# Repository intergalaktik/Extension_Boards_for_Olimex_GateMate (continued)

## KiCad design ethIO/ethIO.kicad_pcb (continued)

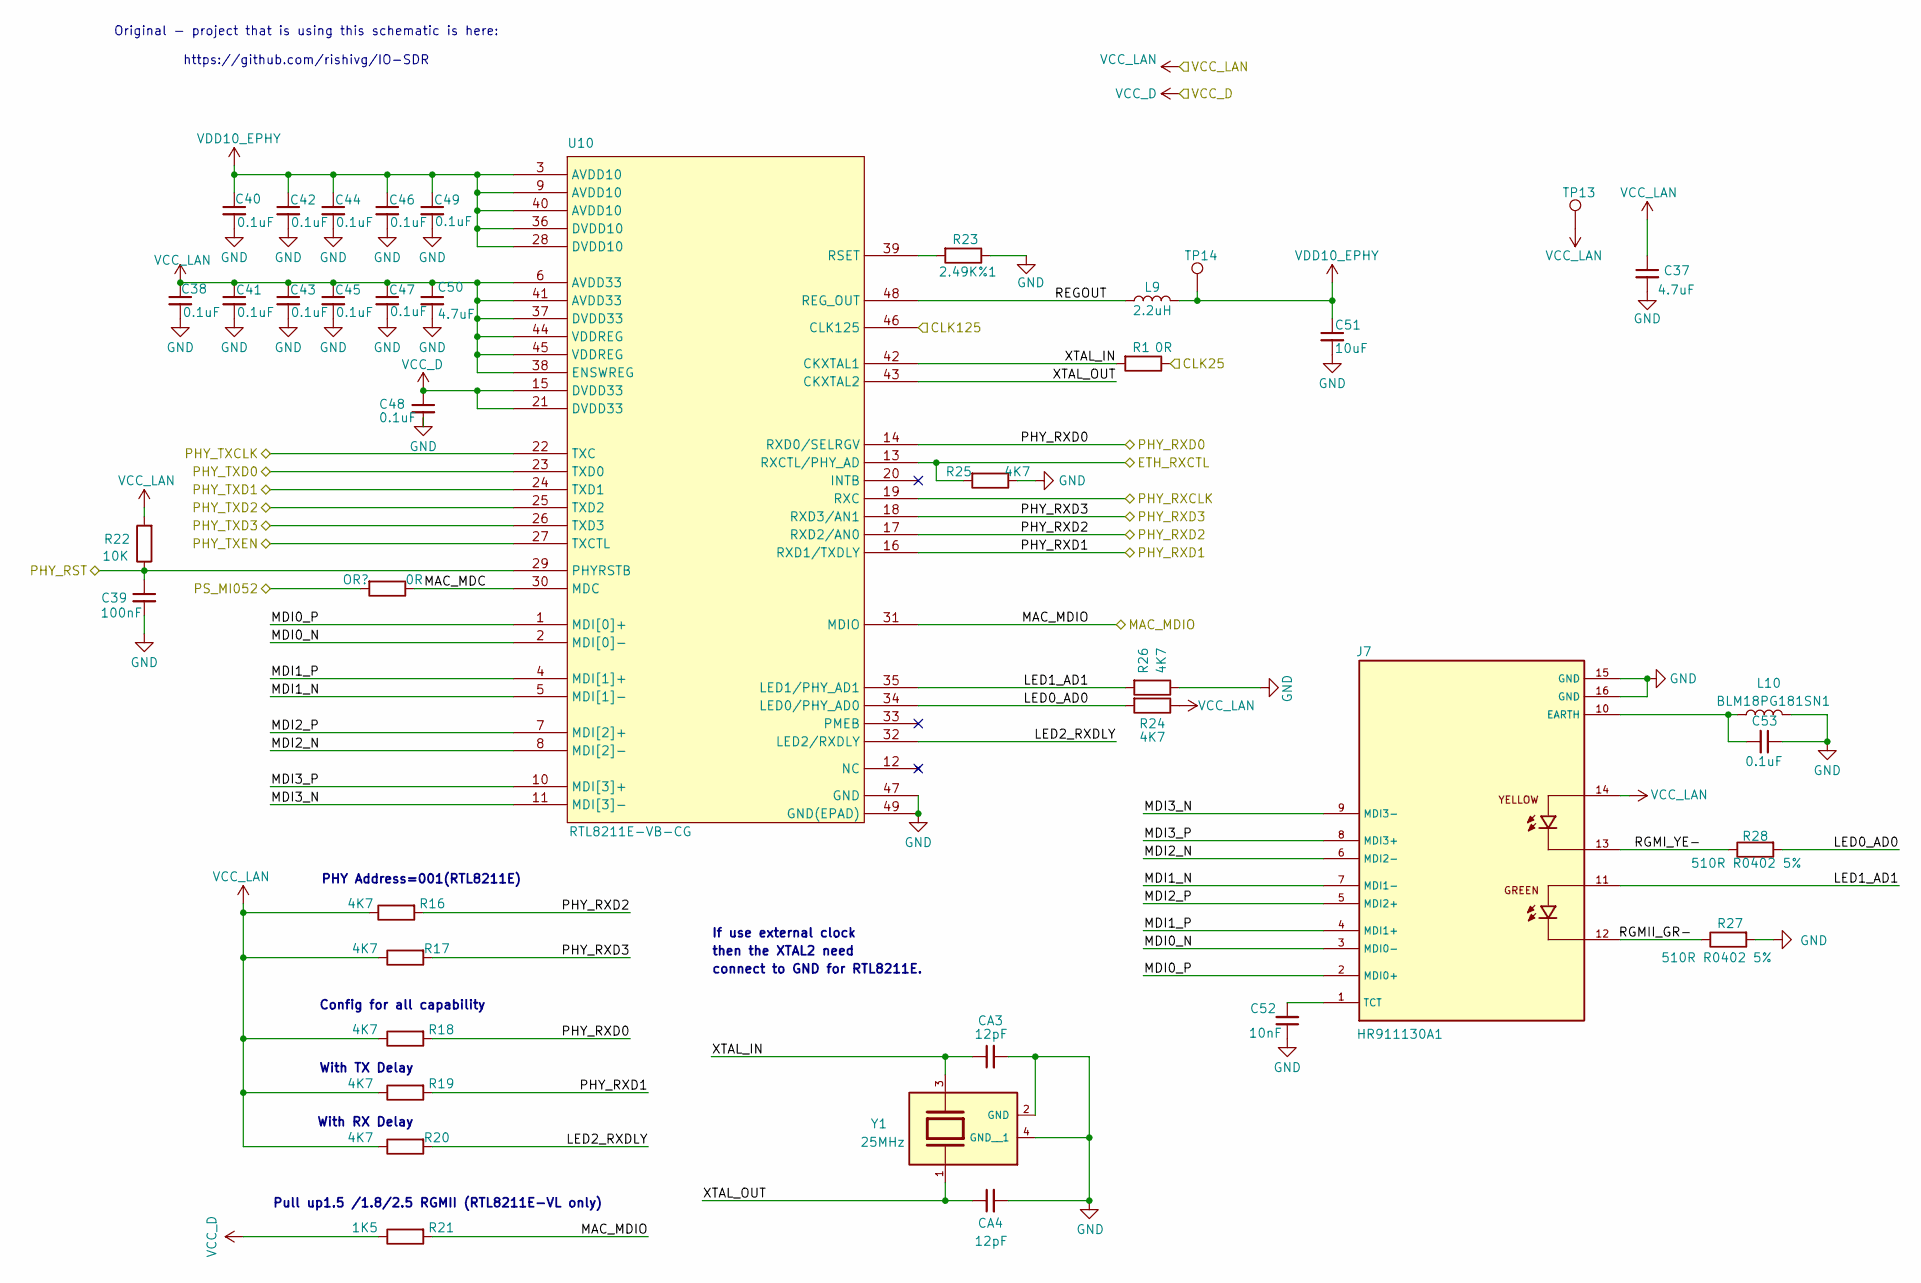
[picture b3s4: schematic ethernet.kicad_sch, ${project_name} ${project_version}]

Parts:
C37, C50: 4.7uF; C_0603_1608Metric_Pad1.08x0.95mm_HandSolder
C38, C40, C41, C42, C43, C44, C45, C46, C47, C48, C49: 0.1uF; C_0402_1005Metric_Pad0.74x0.62mm_HandSolder
C39: 100nF; C_0402_1005Metric_Pad0.74x0.62mm_HandSolder
C51: 10uF; C_0805_2012Metric_Pad1.18x1.45mm_HandSolder
C52: 10nF; C_0402_1005Metric_Pad0.74x0.62mm_HandSolder
C53: 0.1uF; C_0805_2012Metric_Pad1.18x1.45mm_HandSolder
CA3, CA4: 12pF; C_0402_1005Metric_Pad0.74x0.62mm_HandSolder
J7: HR911130A1; HR911130A_HAN
L9: 2.2uH; L_0603_1608Metric_Pad1.05x0.95mm_HandSolder
L10: BLM18PG181SN1; L_0603_1608Metric_Pad1.05x0.95mm_HandSolder
R1: 0R; R_0402_1005Metric_Pad0.72x0.64mm_HandSolder
R16, R17, R18, R19, R20, R24, R25, R26: 4K7; R_0402_1005Metric_Pad0.72x0.64mm_HandSolder
R21: 1K5; R_0402_1005Metric_Pad0.72x0.64mm_HandSolder
R22: 10K; R_0402_1005Metric_Pad0.72x0.64mm_HandSolder
R23: 2.49K%1; R_0402_1005Metric_Pad0.72x0.64mm_HandSolder
R27, R28: 510R R0402 5%; R_0402_1005Metric_Pad0.72x0.64mm_HandSolder
RA5: 0R; R_0603_1608Metric_Pad0.98x0.95mm_HandSolder
TP13, TP14: TestPoint; TestPoint_Pad_D1.0mm
U10: RTL8211E-VB-CG
Y1: 25MHz; Crystal_SMD_SeikoEpson_TSX3225-4Pin_3.2x2.5mm; PARTREV N/A

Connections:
+VCC_HIGH: C37.1, C38.1, C41.1, C43.1, C45.1, C47.1, C50.1, J7.14, R16.1, R17.1, R18.1, R19.1, R20.1, R22.2, R24.1, TP13.1, U10.6 (AVDD33), U10.37 (DVDD33), U10.38 (ENSWREG), U10.41 (AVDD33), U10.44 (VDDREG), U10.45 (VDDREG); also elsewhere on the board
+VCC_LOW: C48.1, R21.1, U10.15 (DVDD33), U10.21 (DVDD33); also elsewhere on the board
/Main Sheet/Ethernet/LED0_AD0: R24.2, R28.2, U10.34 (LED0/PHY_AD0)
/Main Sheet/Ethernet/LED1_AD1: J7.11, R26.2, U10.35 (LED1/PHY_AD1)
/Main Sheet/Ethernet/LED2_RXDLY: R20.2, U10.32 (LED2/RXDLY)
/Main Sheet/Ethernet/MAC_MDC: U10.30 (MDC); also elsewhere on the board
/Main Sheet/Ethernet/MDI0_N: J7.3 (MDI0-), U10.2 (MDI[0]-)
/Main Sheet/Ethernet/MDI0_P: J7.2 (MDI0+), U10.1 (MDI[0]+)
/Main Sheet/Ethernet/MDI1_N: J7.7 (MDI1-), U10.5 (MDI[1]-)
/Main Sheet/Ethernet/MDI1_P: J7.4 (MDI1+), U10.4 (MDI[1]+)
/Main Sheet/Ethernet/MDI2_N: J7.6 (MDI2-), U10.8 (MDI[2]-)
/Main Sheet/Ethernet/MDI2_P: J7.5 (MDI2+), U10.7 (MDI[2]+)
/Main Sheet/Ethernet/MDI3_N: J7.9 (MDI3-), U10.11 (MDI[3]-)
/Main Sheet/Ethernet/MDI3_P: J7.8 (MDI3+), U10.10 (MDI[3]+)
/Main Sheet/Ethernet/REGOUT: L9.1, U10.48 (REG_OUT)
/Main Sheet/Ethernet/RGMII_GR-: J7.12, R27.1
/Main Sheet/Ethernet/RGMI_YE-: J7.13, R28.1
/Main Sheet/Ethernet/XTAL_IN: CA3.1, R1.2, U10.42 (CKXTAL1), Y1.3
/Main Sheet/Ethernet/XTAL_OUT: CA4.1, U10.43 (CKXTAL2), Y1.1
/Main Sheet/NB_A0_0P: R25.2, U10.13 (RXCTL/PHY_AD); also elsewhere on the board
/Main Sheet/NB_A1_1P: R21.2, U10.31 (MDIO); also elsewhere on the board
/Main Sheet/NB_A2_2P: R16.2, U10.17 (RXD2/AN0); also elsewhere on the board
/Main Sheet/NB_A3_3P: U10.19 (RXC); also elsewhere on the board
/Main Sheet/NB_A4_4P: U10.23 (TXD0); also elsewhere on the board
/Main Sheet/NB_A5_5P: U10.25 (TXD2); also elsewhere on the board
/Main Sheet/NB_A6_6P: U10.27 (TXCTL); also elsewhere on the board
/Main Sheet/NB_A8_8P: U10.46 (CLK125); also elsewhere on the board
/Main Sheet/NB_B0_0N: R18.2, U10.14 (RXD0/SELRGV); also elsewhere on the board
/Main Sheet/NB_B1_1N: R19.2, U10.16 (RXD1/TXDLY); also elsewhere on the board
/Main Sheet/NB_B2_2N: R17.2, U10.18 (RXD3/AN1); also elsewhere on the board
/Main Sheet/NB_B3_3N: U10.22 (TXC); also elsewhere on the board
/Main Sheet/NB_B4_4N: U10.24 (TXD1); also elsewhere on the board
/Main Sheet/NB_B5_5N: U10.26 (TXD3); also elsewhere on the board
/Main Sheet/NB_B6_6N: C39.1, R22.1, U10.29 (PHYRSTB); also elsewhere on the board
/Main Sheet/NB_B7_7N: R1.1; also elsewhere on the board
GND: C37.2, C38.2, C39.2, C40.2, C41.2, C42.2, C43.2, C44.2, C45.2, C46.2, C47.2, C48.2, C49.2, C50.2, C51.2, C52.1, C53.1, CA3.2, CA4.2, J7.15 (GND), J7.16 (GND), L10.1, R23.1, R25.1, R26.1, R27.2, U10.47 (GND), U10.49 (GND(EPAD)), Y1.2 (GND), Y1.4 (GND__1); also elsewhere on the board
unnamed: C53.2, J7.10 (EARTH), L10.2
unnamed: C52.2, J7.1 (TCT)
unnamed: R23.2, U10.39 (RSET)
VDD10_EPHY: C40.1, C42.1, C44.1, C46.1, C49.1, C51.1, L9.2, TP14.1, U10.3 (AVDD10), U10.9 (AVDD10), U10.28 (DVDD10), U10.36 (DVDD10), U10.40 (AVDD10)

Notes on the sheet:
then the XTAL2 need
PHY Address=001(RTL8211E)
With RX Delay
Pull up1.5 /1.8/2.5 RGMII (RTL8211E-VL only)
connect to GND for RTL8211E.
If use external clock
Original - project that is using this schematic is here: https://github.com/rishivg/IO-SDR
Config for all capability
With TX Delay

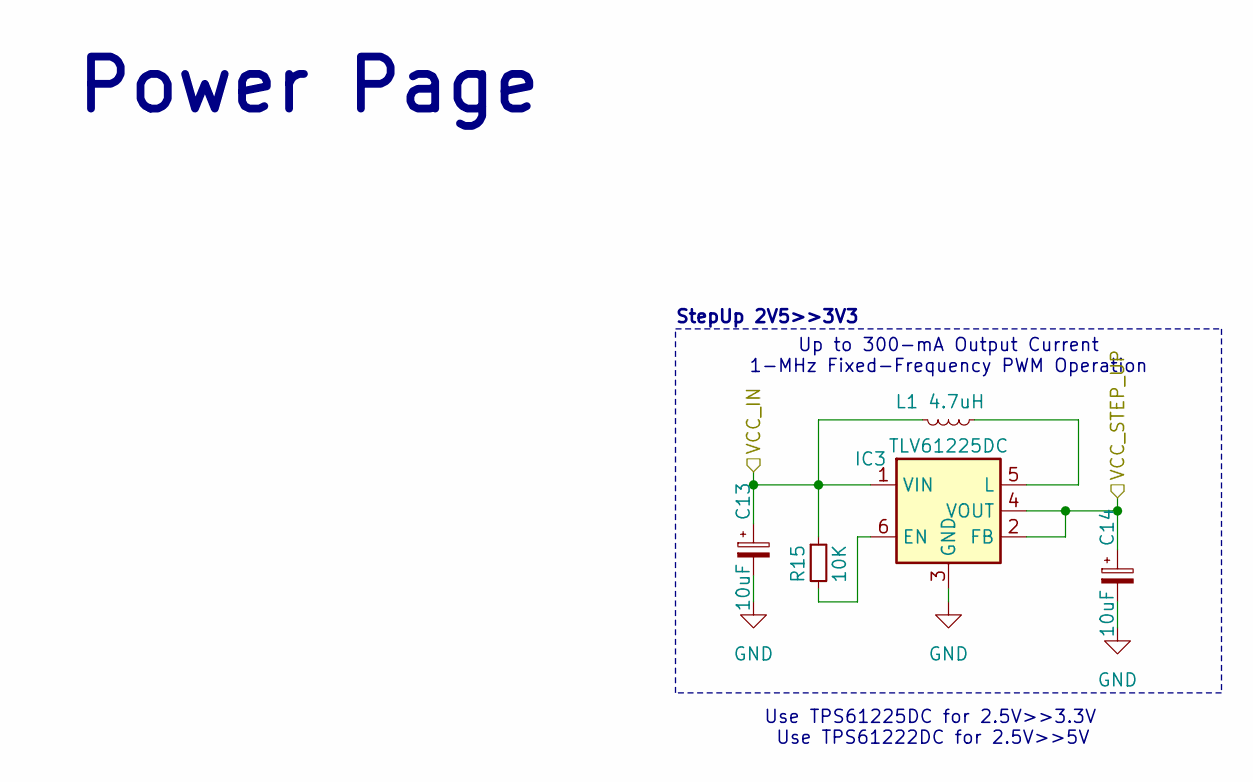
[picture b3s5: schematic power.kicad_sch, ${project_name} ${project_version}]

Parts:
C13, C14: 10uF; C_0603_1608Metric
IC3: TLV61225DC; SOT-363_SC-70-6
L1: 4.7uH; L_0603_1608Metric
R15: 10K; R_0402_1005Metric; MPN RC0603FR-071K1L; Mouser 603-RC0603FR-071K1L

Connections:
+VCC_HIGH: C14.1, IC3.2 (FB), IC3.4 (VOUT); also elsewhere on the board
+VCC_LOW: C13.1, IC3.1 (VIN), L1.2, R15.1; also elsewhere on the board
GND: C13.2, C14.2, IC3.3 (GND); also elsewhere on the board
unnamed: IC3.6 (EN), R15.2
unnamed: IC3.5 (L), L1.1

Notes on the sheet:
Up to 300-mA Output Current 1-MHz Fixed-Frequency PWM Operation
Use TPS61222DC for 2.5V>>5V
Power Page
StepUp 2V5>>3V3
Use TPS61225DC for 2.5V>>3.3V

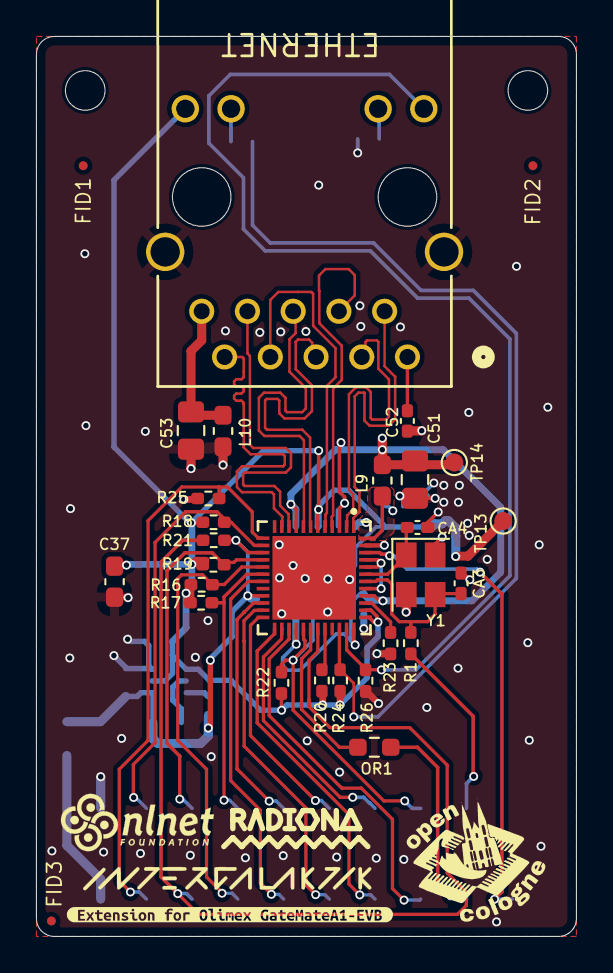
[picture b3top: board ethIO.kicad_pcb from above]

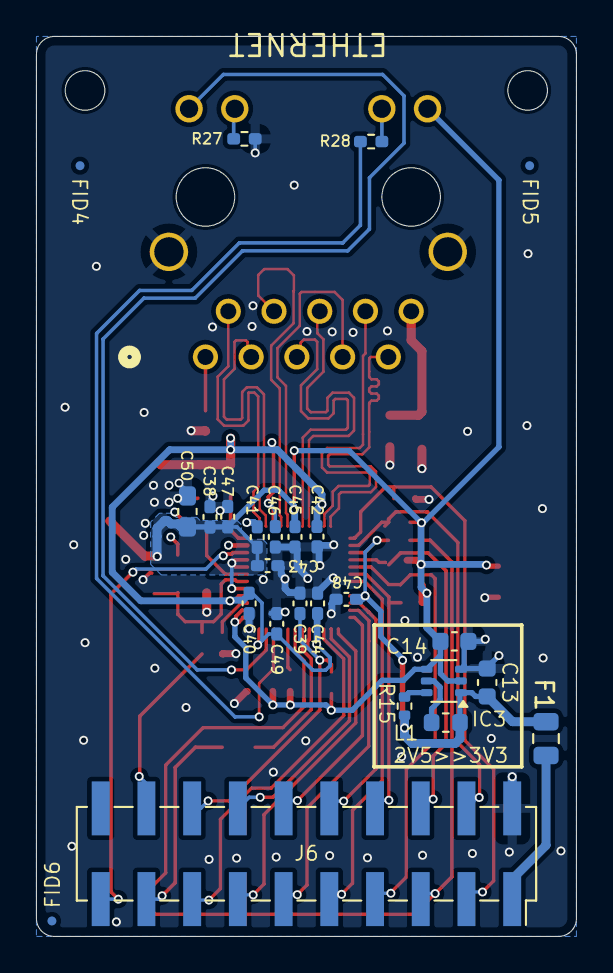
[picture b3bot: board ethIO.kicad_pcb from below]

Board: 4 copper layers, 30.0 x 50.0 mm, 61 parts (25 on the bottom side), 44 nets.

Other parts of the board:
OR1: 0R; R_0603_1608Metric_Pad0.98x0.95mm_HandSolder
kibuzzard-674D68C8: G***; kibuzzard-674D68C8

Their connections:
/Main Sheet/Ethernet/MAC_MDC: OR1.1; also elsewhere on the board
/Main Sheet/NB_A7_7P: OR1.2; also elsewhere on the board

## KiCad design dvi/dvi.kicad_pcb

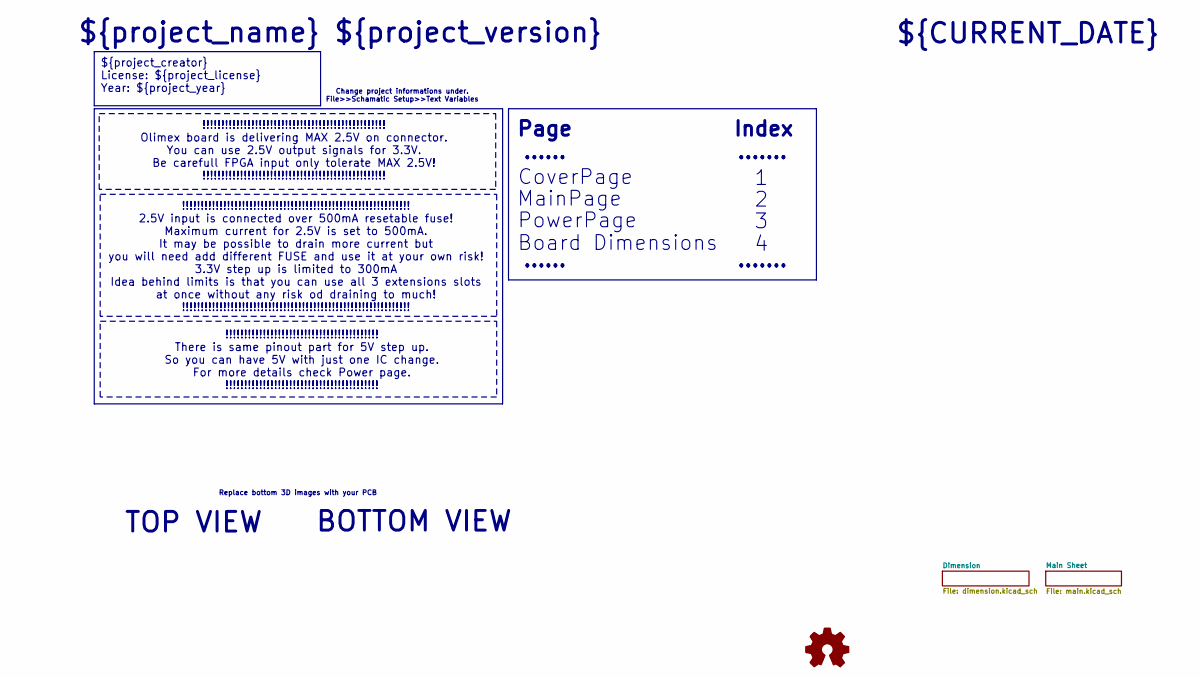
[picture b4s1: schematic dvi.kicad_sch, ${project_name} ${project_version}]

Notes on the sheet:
${project_creator} License: ${project_license} Year: ${project_year}
BOTTOM VIEW
Replace bottom 3D images with your PCB
Index
!!!!!!!!!!!!!!!!!!!!!!!!!!!!!!!!!!!!!!!!!!!!!!!!!!!!!!!!!!!!! 2.5V input is connected over 500mA resetable fuse! Maximum current for 2.5V is set to 500mA. It may be possible to drain more current but you will need add different FUSE and use it at your own risk! 3.3V step up is limited to 300mA Idea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
!!!!!!!!!!!!!!!!!!!!!!!!!!!!!!!!!!!!!!!!!!!!!!!!! Olimex board is delivering MAX 2.5V on connector. You can use 2.5V output signals for 3.3V. Be carefull FPGA input only tolerate MAX 2.5V! !!!!!!!!!!!!!!!!!!!!!!!!!!!!!!!!!!!!!!!!!!!!!!!!!
!!!!!!!!!!!!!!!!!!!!!!!!!!!!!!!!!!!!!!!!! There is same pinout part for 5V step up. So you can have 5V with just one IC change. For more details check Power page. !!!!!!!!!!!!!!!!!!!!!!!!!!!!!!!!!!!!!!!!!
......
PowerPage
Change project informations under. File>>Schamatic Setup>>Text Variables
.......
CoverPage
Board Dimensions
MainPage
${CURRENT_DATE}
${project_name} ${project_version}
TOP VIEW
Page

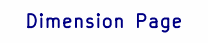
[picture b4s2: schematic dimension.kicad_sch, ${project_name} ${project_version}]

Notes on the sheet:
Dimension Page

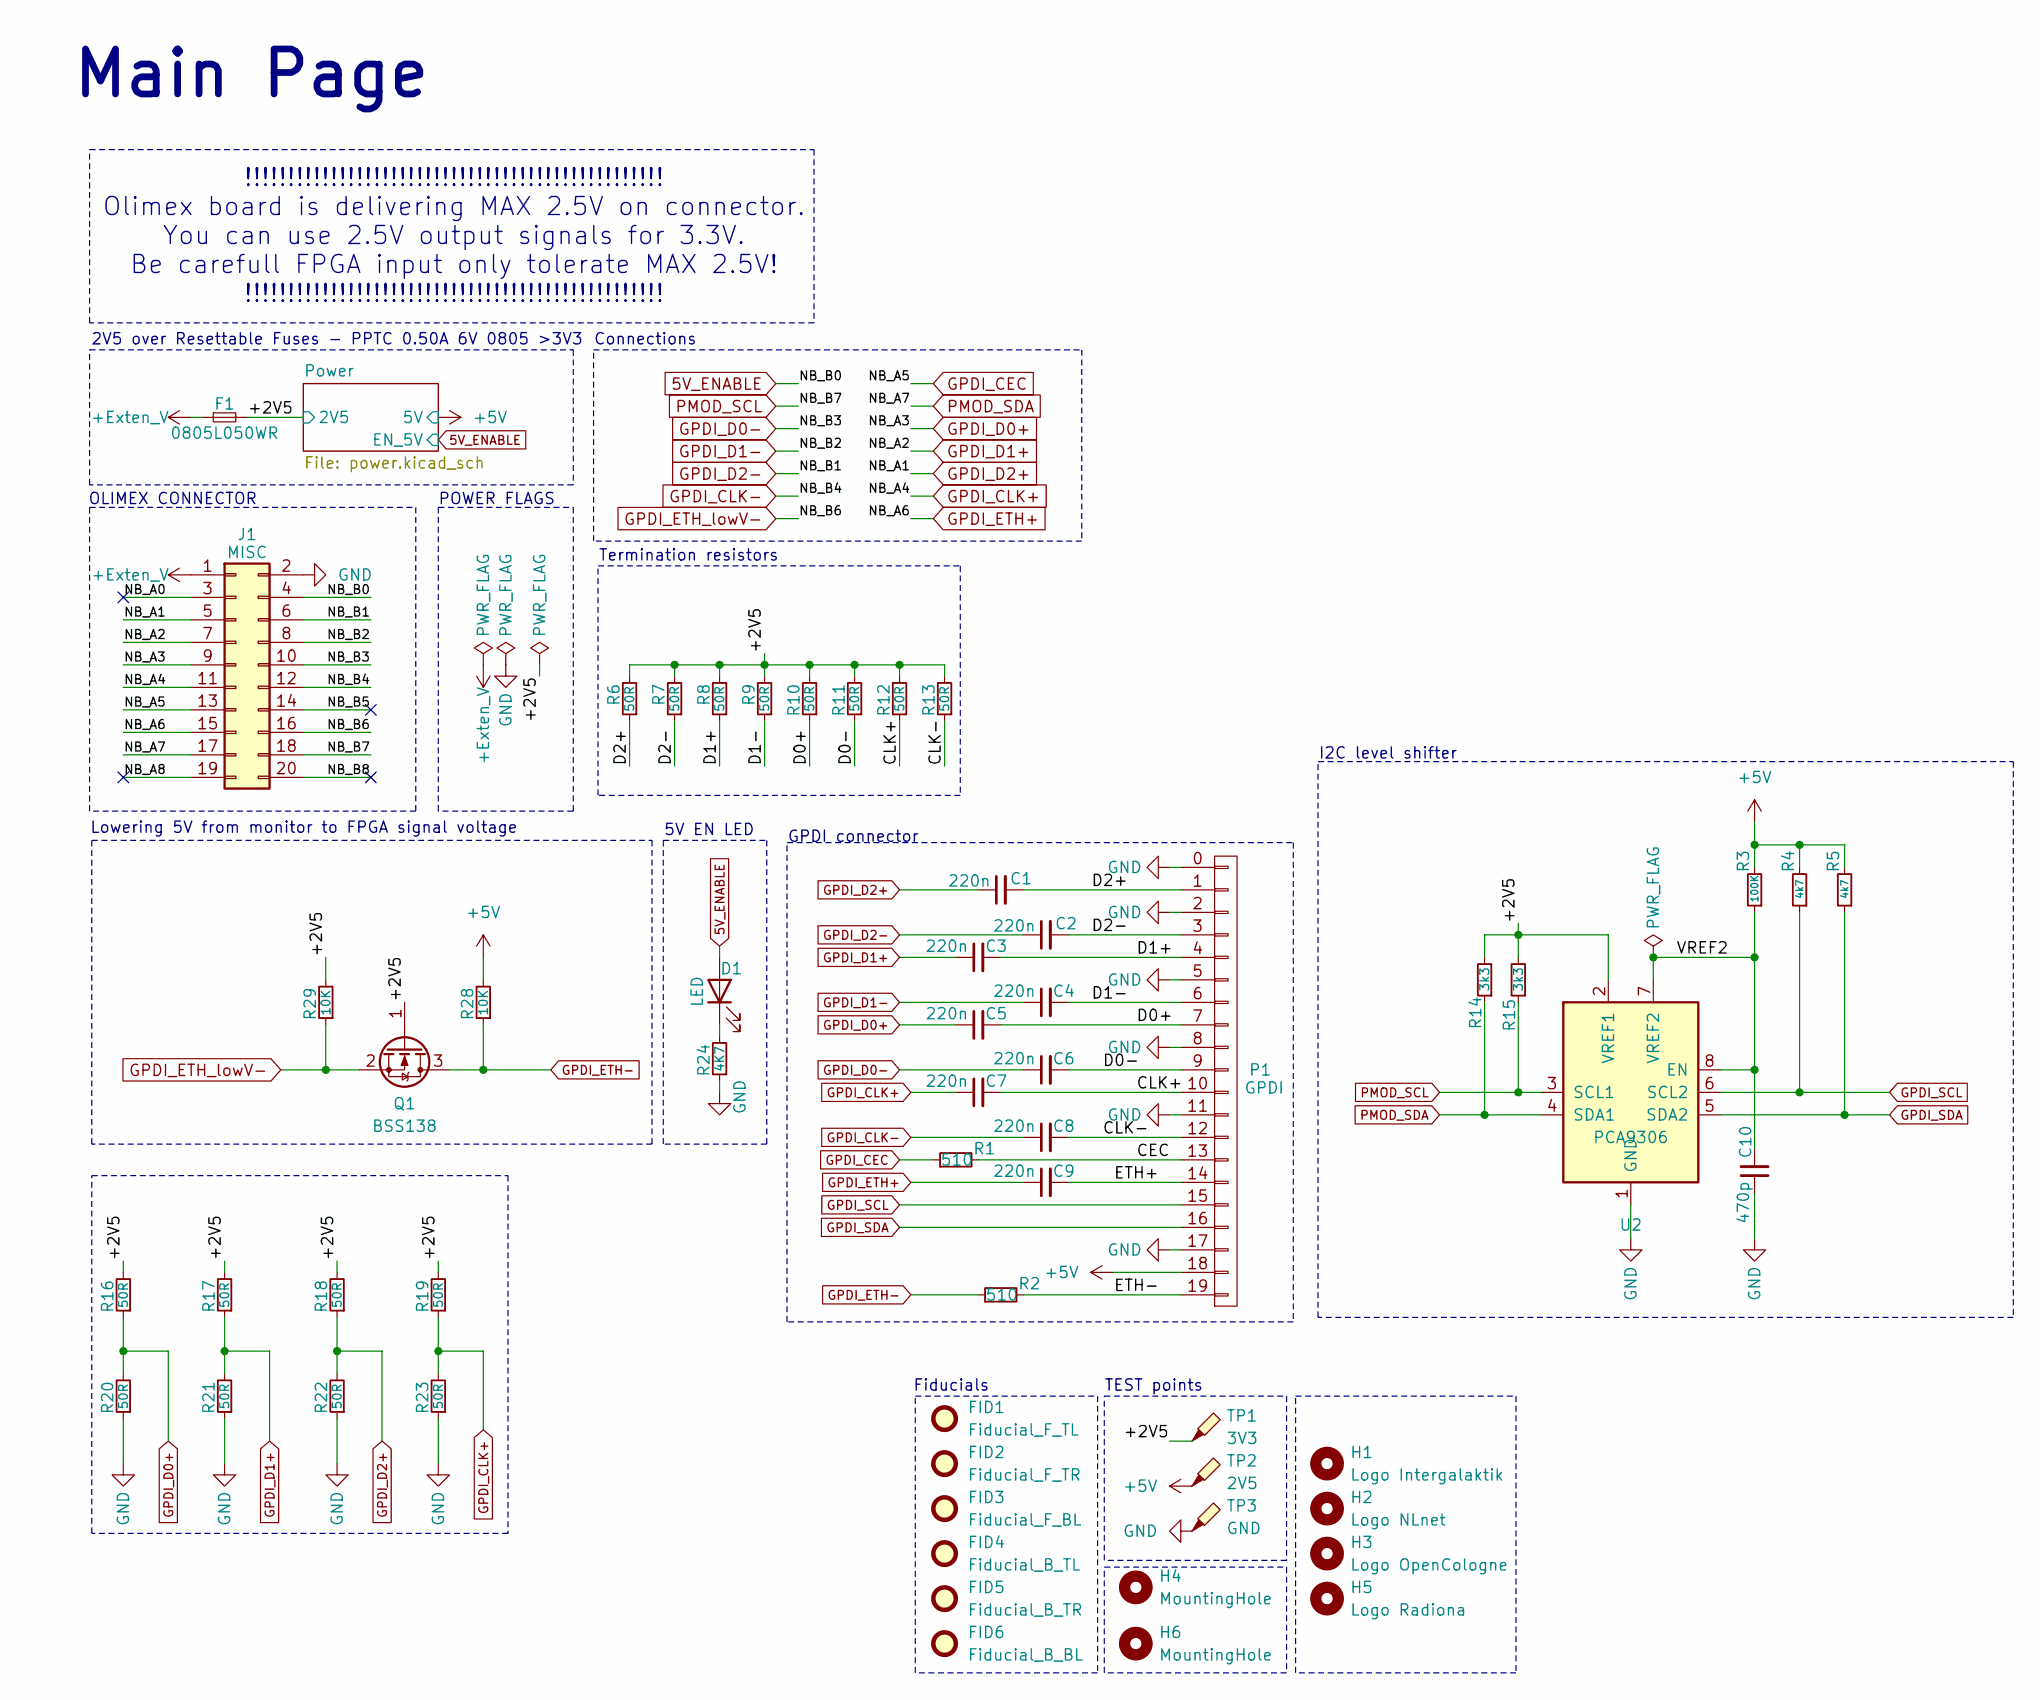
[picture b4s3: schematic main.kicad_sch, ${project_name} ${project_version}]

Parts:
C1, C2, C3, C4, C5, C6, C7, C8, C9: 220n; C_0402_1005Metric
C10: 470p; C_0402_1005Metric
D1: LED; LED_0603_1608Metric
F1: 0805L050WR; Fuse_0805_2012Metric
FID1: Fiducial_F_TL; Fiducial_0.5mm_Mask1mm
FID2: Fiducial_F_TR; Fiducial_0.5mm_Mask1mm
FID3: Fiducial_F_BL; Fiducial_0.5mm_Mask1mm
FID4: Fiducial_B_TL; Fiducial_0.5mm_Mask1mm
FID5: Fiducial_B_TR; Fiducial_0.5mm_Mask1mm
FID6: Fiducial_B_BL; Fiducial_0.5mm_Mask1mm
H1: Logo Intergalaktik; intergalaktik
H2: Logo NLnet; nlnet
H3: Logo OpenCologne; open_cologne_small
H4, H6: MountingHole; MountingHole_2.2mm_M2
H5: Logo Radiona; radiona_small
J1: MISC; PinSocket_2x10_P2.54mm_Vertical_SMD
P1: GPDI; CONN-10029449-111RLF
Q1: BSS138; SOT-23
R1, R2: 510; R_0402_1005Metric; MPN RC0603FR-071K1L; Mouser 603-RC0603FR-071K1L
R3: 100K; R_0402_1005Metric; MPN RC0603FR-071K1L; Mouser 603-RC0603FR-071K1L
R4, R5: 4k7; R_0402_1005Metric; MPN RC0603FR-071K1L; Mouser 603-RC0603FR-071K1L
R6, R7, R8, R9, R10, R11, R12, R13, R16, R17, R18, R19, R20, R21, R22, R23: 50R; R_0402_1005Metric; MPN RC0603FR-071K1L; Mouser 603-RC0603FR-071K1L
R14, R15: 3k3; R_0402_1005Metric; MPN RC0603FR-071K1L; Mouser 603-RC0603FR-071K1L
R24: 4K7; R_0402_1005Metric; MPN RC0603FR-071K1L; Mouser 603-RC0603FR-071K1L
R28, R29: 10K; R_0402_1005Metric; MPN RC0603FR-071K1L; Mouser 603-RC0603FR-071K1L
TP1: 3V3; TestPoint_Pad_D1.0mm
TP2: 2V5; TestPoint_Pad_D1.0mm
TP3: GND; TestPoint_Pad_D1.0mm
U2: PCA9306; SSOP-8_2.95x2.8mm_P0.65mm

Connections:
5V_ENABLE: D1.2 (A), J1.4; also elsewhere on the board
+5V: P1.18, R3.2, R4.2, R5.2, R28.2, TP2.1; also elsewhere on the board
+Exten_V: F1.1, J1.1
/Main Sheet/+2V5: F1.2, Q1.1 (G), R6.2, R7.2, R8.2, R9.2, R10.2, R11.2, R12.2, R13.2, R14.2, R15.2, R16.2, R17.2, R18.2, R19.2, R29.2, TP1.1; also elsewhere on the board
/Main Sheet/CEC: P1.13, R1.2
/Main Sheet/CLK+: C7.2, P1.10, R12.1
/Main Sheet/CLK-: C8.2, P1.12, R13.1
/Main Sheet/D0+: C5.2, P1.7, R10.1
/Main Sheet/D0-: C6.2, P1.9, R11.1
/Main Sheet/D1+: C3.2, P1.4, R8.1
/Main Sheet/D1-: C4.2, P1.6, R9.1
/Main Sheet/D2+: C1.2, P1.1, R6.1
/Main Sheet/D2-: C2.2, P1.3, R7.1
/Main Sheet/ETH+: C9.2, P1.14
/Main Sheet/ETH-: P1.19, R2.2
/Main Sheet/NB_A0: J1.3
/Main Sheet/NB_A8: J1.19
/Main Sheet/NB_B5: J1.14
/Main Sheet/NB_B8: J1.20
/Main Sheet/VREF2: C10.2, R3.1; also elsewhere on the board
GND: C10.1, J1.2, P1.0, P1.2, P1.5, P1.8, P1.11, P1.17, R20.1, R21.1, R22.1, R23.1, R24.1, TP3.1; also elsewhere on the board
GPDI_CEC: J1.13, R1.1
GPDI_CLK+: C7.1, J1.11, R19.1, R23.2
GPDI_CLK-: C8.1, J1.12
GPDI_D0+: C5.1, J1.9, R16.1, R20.2
GPDI_D0-: C6.1, J1.10
GPDI_D1+: C3.1, J1.7, R17.1, R21.2
GPDI_D1-: C4.1, J1.8
GPDI_D2+: C1.1, J1.5, R18.1, R22.2
GPDI_D2-: C2.1, J1.6
GPDI_ETH+: C9.1, J1.15
GPDI_ETH-: Q1.3 (D), R2.1, R28.1
GPDI_ETH_lowV-: J1.16, Q1.2 (S), R29.1
GPDI_SCL: P1.15, R4.1; also elsewhere on the board
GPDI_SDA: P1.16, R5.1; also elsewhere on the board
unnamed: D1.1 (K), R24.2
PMOD_SCL: J1.18, R15.1; also elsewhere on the board
PMOD_SDA: J1.17, R14.1; also elsewhere on the board

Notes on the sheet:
TEST points
POWER FLAGS
2V5 over Resettable Fuses - PPTC 0.50A 6V 0805 >3V3
!!!!!!!!!!!!!!!!!!!!!!!!!!!!!!!!!!!!!!!!!!!!!!!!! Olimex board is delivering MAX 2.5V on connector. You can use 2.5V output signals for 3.3V. Be carefull FPGA input only tolerate MAX 2.5V! !!!!!!!!!!!!!!!!!!!!!!!!!!!!!!!!!!!!!!!!!!!!!!!!!
Termination resistors
GPDI connector
Fiducials
I2C level shifter
Lowering 5V from monitor to FPGA signal voltage
OLIMEX CONNECTOR
Connections
5V EN LED
Main Page

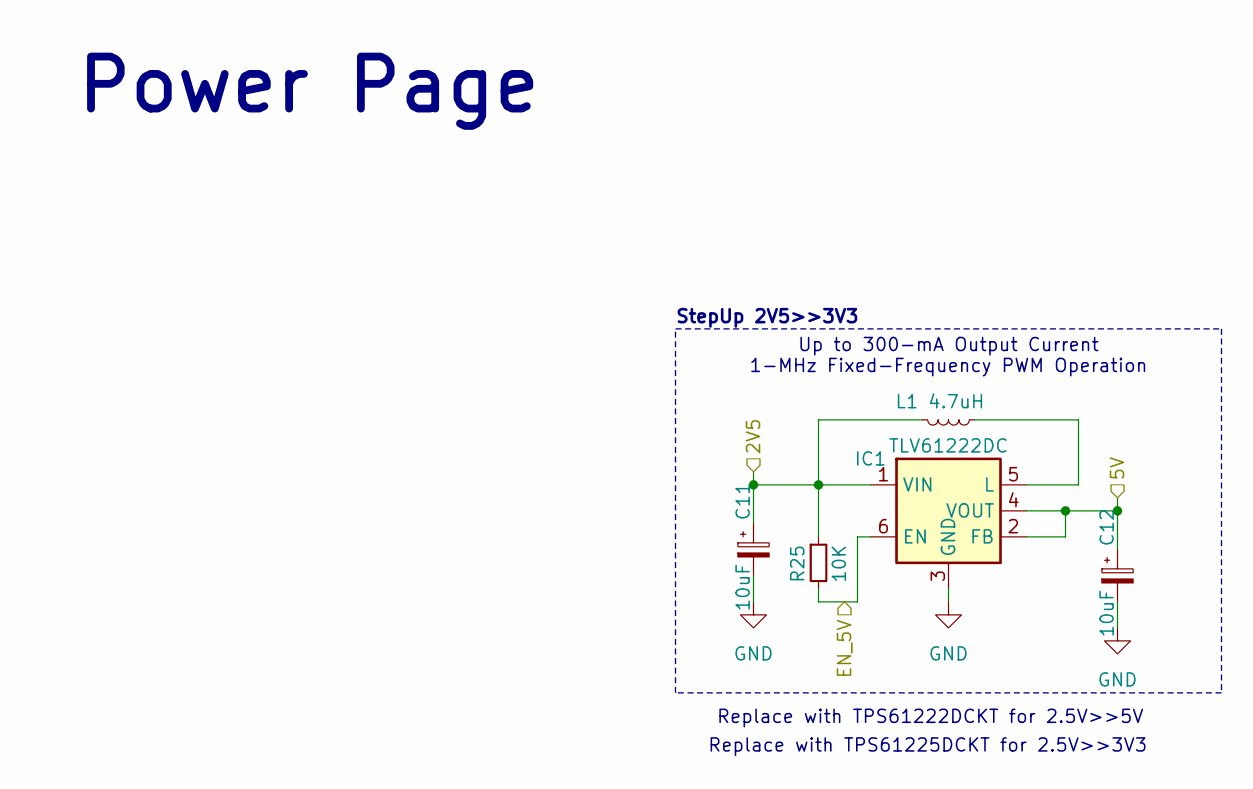
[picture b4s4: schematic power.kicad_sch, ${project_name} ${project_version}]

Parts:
C11, C12: 10uF; C_0603_1608Metric
IC1: TLV61222DC; SOT-363_SC-70-6
L1: 4.7uH; L_0603_1608Metric
R25: 10K; R_0402_1005Metric; MPN RC0603FR-071K1L; Mouser 603-RC0603FR-071K1L

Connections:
5V_ENABLE: IC1.6 (EN), R25.2; also elsewhere on the board
+5V: C12.1, IC1.2 (FB), IC1.4 (VOUT); also elsewhere on the board
/Main Sheet/+2V5: C11.1, IC1.1 (VIN), L1.2, R25.1; also elsewhere on the board
GND: C11.2, C12.2, IC1.3 (GND); also elsewhere on the board
unnamed: IC1.5 (L), L1.1

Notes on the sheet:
Up to 300-mA Output Current 1-MHz Fixed-Frequency PWM Operation
Power Page
StepUp 2V5>>3V3
Replace with TPS61225DCKT for 2.5V>>3V3
Replace with TPS61222DCKT for 2.5V>>5V

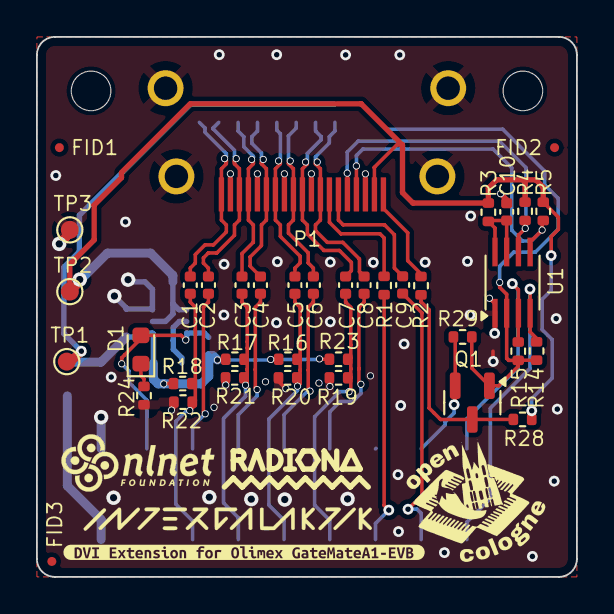
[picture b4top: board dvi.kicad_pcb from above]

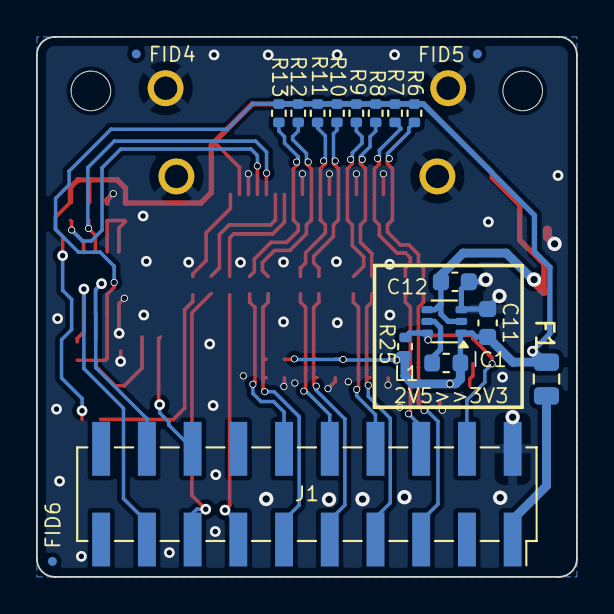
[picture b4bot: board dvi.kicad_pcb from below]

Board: 4 copper layers, 30.0 x 30.0 mm, 63 parts (18 on the bottom side), 35 nets.

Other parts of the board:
U1: PCA9306; SSOP-8_2.95x2.8mm_P0.65mm
kibuzzard-6750A0AE: G***; kibuzzard-6750A0AE

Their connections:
/Main Sheet/+2V5: U1.2 (VREF1); also elsewhere on the board
/Main Sheet/VREF2: U1.7 (VREF2), U1.8 (EN); also elsewhere on the board
GND: U1.1 (GND); also elsewhere on the board
GPDI_SCL: U1.6 (SCL2); also elsewhere on the board
GPDI_SDA: U1.5 (SDA2); also elsewhere on the board
PMOD_SCL: U1.3 (SCL1); also elsewhere on the board
PMOD_SDA: U1.4 (SDA1); also elsewhere on the board

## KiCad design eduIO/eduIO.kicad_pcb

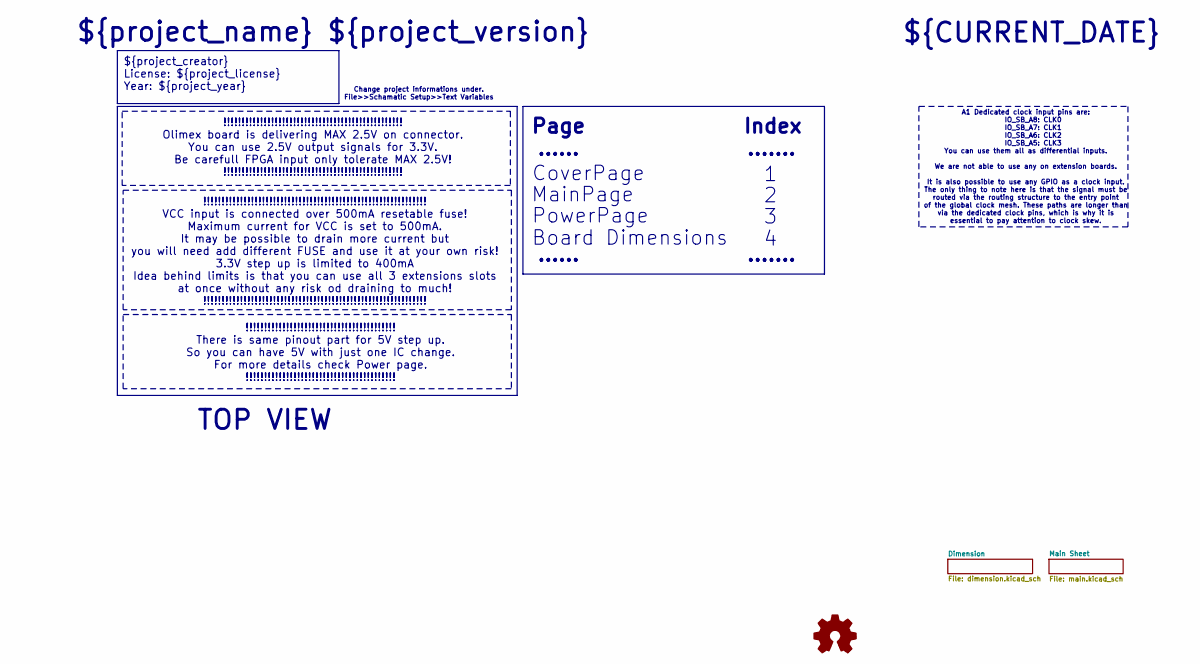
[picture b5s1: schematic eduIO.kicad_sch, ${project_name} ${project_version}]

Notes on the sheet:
${project_creator} License: ${project_license} Year: ${project_year}
Index
!!!!!!!!!!!!!!!!!!!!!!!!!!!!!!!!!!!!!!!!!!!!!!!!!!!!!!!!!!!!! VCC input is connected over 500mA resetable fuse! Maximum current for VCC is set to 500mA. It may be possible to drain more current but you will need add different FUSE and use it at your own risk! 3.3V step up is limited to 400mA Idea b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
!!!!!!!!!!!!!!!!!!!!!!!!!!!!!!!!!!!!!!!!!!!!!!!!! Olimex board is delivering MAX 2.5V on connector. You can use 2.5V output signals for 3.3V. Be carefull FPGA input only tolerate MAX 2.5V! !!!!!!!!!!!!!!!!!!!!!!!!!!!!!!!!!!!!!!!!!!!!!!!!!
!!!!!!!!!!!!!!!!!!!!!!!!!!!!!!!!!!!!!!!!! There is same pinout part for 5V step up. So you can have 5V with just one IC change. For more details check Power page. !!!!!!!!!!!!!!!!!!!!!!!!!!!!!!!!!!!!!!!!!
......
PowerPage
Change project informations under. File>>Schamatic Setup>>Text Variables
.......
A1 Dedicated clock input pins are: IO_SB_A8: CLK0 IO_SB_A7: CLK1 IO_SB_A6: CLK2 IO_SB_A5: CLK3 You can use them all as differential inputs. We are not able to use any on extension boards. It is also possible to use any GPIO as a clock input. The only thing to note here is that the signal must be ro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
CoverPage
Board Dimensions
MainPage
${CURRENT_DATE}
${project_name} ${project_version}
TOP VIEW
Page

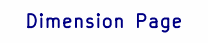
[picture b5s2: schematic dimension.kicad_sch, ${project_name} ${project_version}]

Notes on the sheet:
Dimension Page

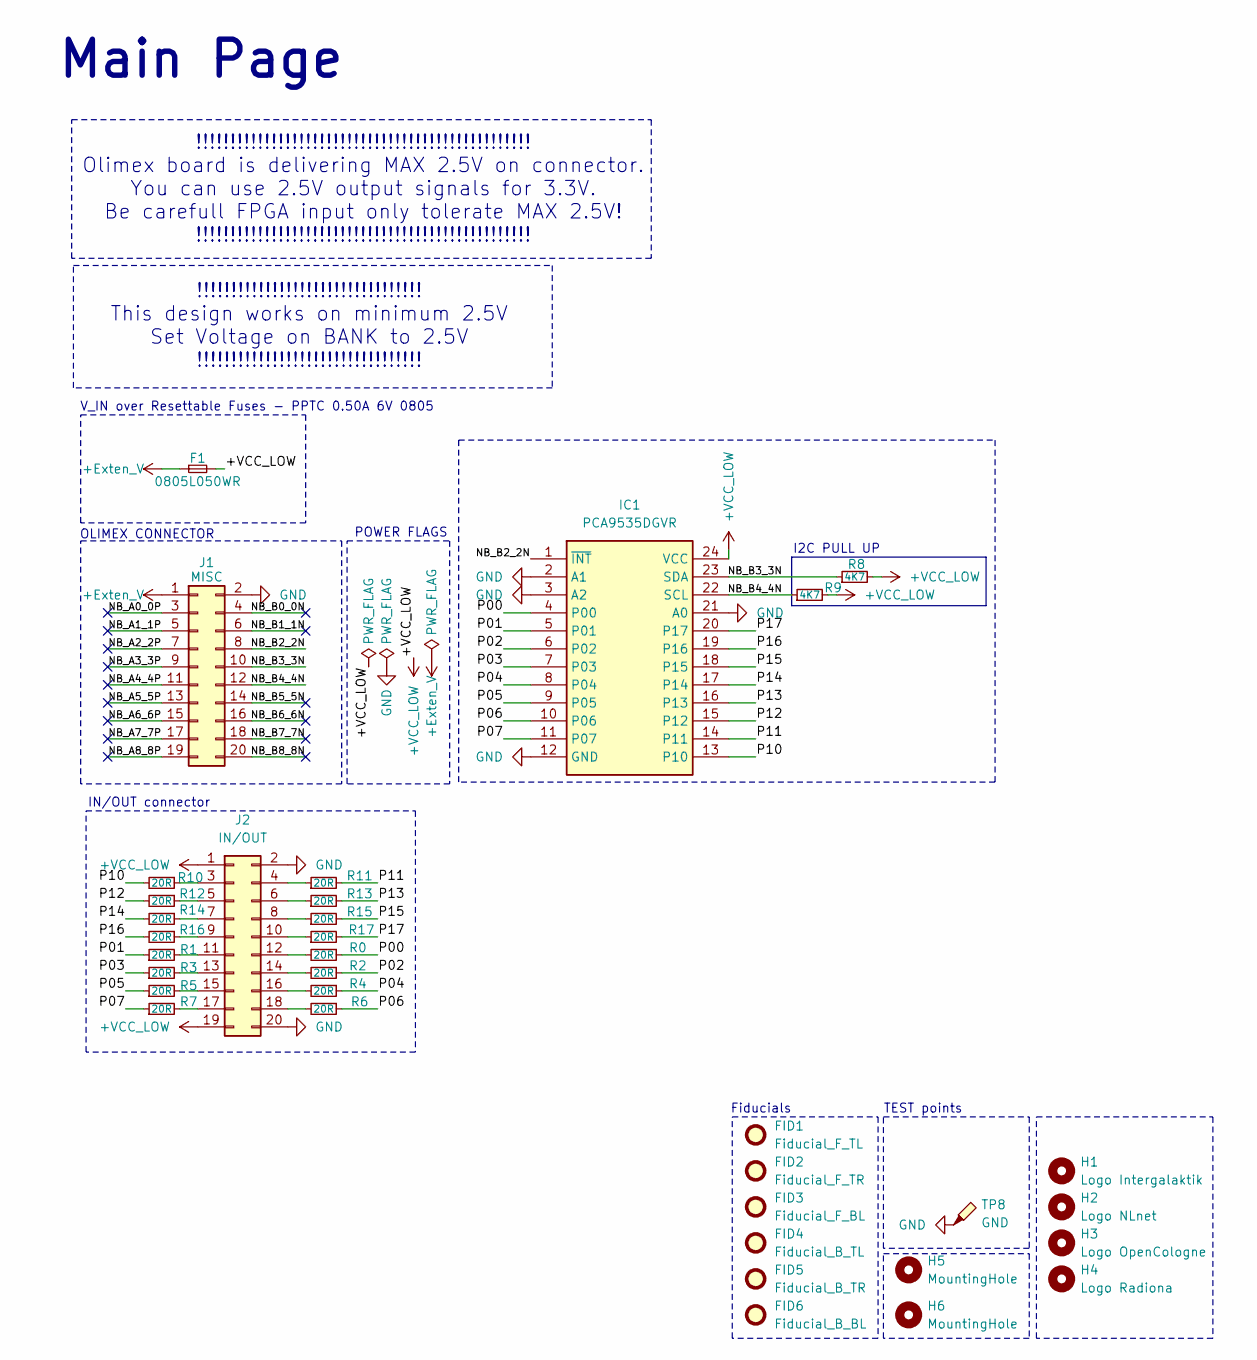
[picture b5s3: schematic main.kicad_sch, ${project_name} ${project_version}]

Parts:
F1: 0805L050WR; Fuse_0805_2012Metric
FID1: Fiducial_F_TL; Fiducial_0.5mm_Mask1mm
FID2: Fiducial_F_TR; Fiducial_0.5mm_Mask1mm
FID3: Fiducial_F_BL; Fiducial_0.5mm_Mask1mm
FID4: Fiducial_B_TL; Fiducial_0.5mm_Mask1mm
FID5: Fiducial_B_TR; Fiducial_0.5mm_Mask1mm
FID6: Fiducial_B_BL; Fiducial_0.5mm_Mask1mm
H1: Logo Intergalaktik; intergalaktik
H2: Logo NLnet; nlnet
H3: Logo OpenCologne; open_cologne_small
H4: Logo Radiona; radiona_small
H5, H6: MountingHole; MountingHole_2.2mm_M2
IC1: PCA9535DGVR; SOP40P640X120-24N; Mouser Part Number 595-PCA9535DGVR
J1: MISC; PinSocket_2x10_P2.54mm_Vertical_SMD
J2: IN/OUT; PinHeader_2x10_P2.54mm_Vertical
R0, R1, R2, R3, R4, R5, R6, R7, R10, R11, R12, R13, R14, R15, R16, R17: 20R; R_0402_1005Metric
R8, R9: 4K7; R_0402_1005Metric
TP8: GND; TestPoint_THTPad_1.0x1.0mm_Drill0.5mm

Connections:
+Exten_V: F1.1, J1.1
+VCC_LOW: F1.2, IC1.24 (VCC), J2.1, J2.19, R8.2, R9.2
/Main Sheet/NB_A0_0P: J1.3
/Main Sheet/NB_A1_1P: J1.5
/Main Sheet/NB_A2_2P: J1.7
/Main Sheet/NB_A3_3P: J1.9
/Main Sheet/NB_A4_4P: J1.11
/Main Sheet/NB_A5_5P: J1.13
/Main Sheet/NB_A6_6P: J1.15
/Main Sheet/NB_A7_7P: J1.17
/Main Sheet/NB_A8_8P: J1.19
/Main Sheet/NB_B0_0N: J1.4
/Main Sheet/NB_B1_1N: J1.6
/Main Sheet/NB_B2_2N: IC1.1 (~INT), J1.8
/Main Sheet/NB_B3_3N: IC1.23 (SDA), J1.10, R8.1
/Main Sheet/NB_B4_4N: IC1.22 (SCL), J1.12, R9.1
/Main Sheet/NB_B5_5N: J1.14
/Main Sheet/NB_B6_6N: J1.16
/Main Sheet/NB_B7_7N: J1.18
/Main Sheet/NB_B8_8N: J1.20
/Main Sheet/P00: IC1.4 (P00), R0.1
/Main Sheet/P01: IC1.5 (P01), R1.1
/Main Sheet/P02: IC1.6 (P02), R2.1
/Main Sheet/P03: IC1.7 (P03), R3.1
/Main Sheet/P04: IC1.8 (P04), R4.1
/Main Sheet/P05: IC1.9 (P05), R5.1
/Main Sheet/P06: IC1.10 (P06), R6.1
/Main Sheet/P07: IC1.11 (P07), R7.1
/Main Sheet/P10: IC1.13 (P10), R10.2
/Main Sheet/P11: IC1.14 (P11), R11.2
/Main Sheet/P12: IC1.15 (P12), R12.2
/Main Sheet/P13: IC1.16 (P13), R13.2
/Main Sheet/P14: IC1.17 (P14), R14.2
/Main Sheet/P15: IC1.18 (P15), R15.2
/Main Sheet/P16: IC1.19 (P16), R16.2
/Main Sheet/P17: IC1.20 (P17), R17.2
GND: IC1.2 (A1), IC1.3 (A2), IC1.12 (GND), IC1.21 (A0), J1.2, J2.2, J2.20, TP8.1
unnamed: J2.3, R10.1
unnamed: J2.4, R11.1
unnamed: J2.5, R12.1
unnamed: J2.6, R13.1
unnamed: J2.7, R14.1
unnamed: J2.8, R15.1
unnamed: J2.9, R16.1
unnamed: J2.10, R17.1
unnamed: J2.11, R1.2
unnamed: J2.12, R0.2
unnamed: J2.13, R3.2
unnamed: J2.14, R2.2
unnamed: J2.15, R5.2
unnamed: J2.16, R4.2
unnamed: J2.17, R7.2
unnamed: J2.18, R6.2

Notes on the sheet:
I2C PULL UP
TEST points
POWER FLAGS
V_IN over Resettable Fuses - PPTC 0.50A 6V 0805
!!!!!!!!!!!!!!!!!!!!!!!!!!!!!!!!!!!!!!!!!!!!!!!!! Olimex board is delivering MAX 2.5V on connector. You can use 2.5V output signals for 3.3V. Be carefull FPGA input only tolerate MAX 2.5V! !!!!!!!!!!!!!!!!!!!!!!!!!!!!!!!!!!!!!!!!!!!!!!!!!
Fiducials
IN/OUT connector
OLIMEX CONNECTOR
Main Page
!!!!!!!!!!!!!!!!!!!!!!!!!!!!!!!!! This design works on minimum 2.5V Set Voltage on BANK to 2.5V !!!!!!!!!!!!!!!!!!!!!!!!!!!!!!!!!

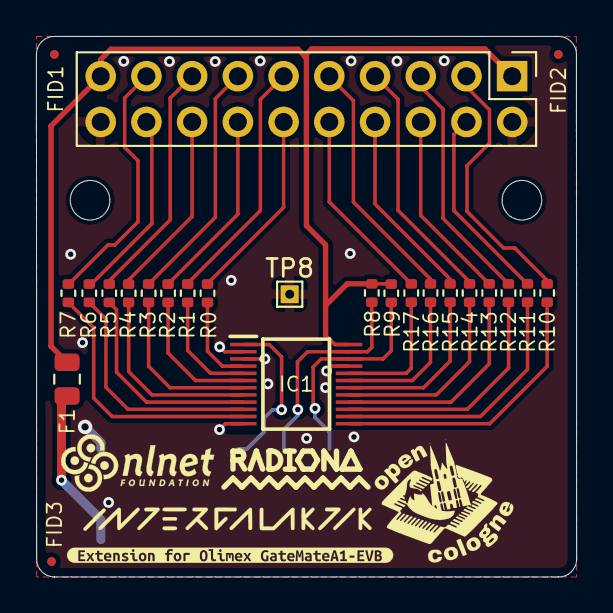
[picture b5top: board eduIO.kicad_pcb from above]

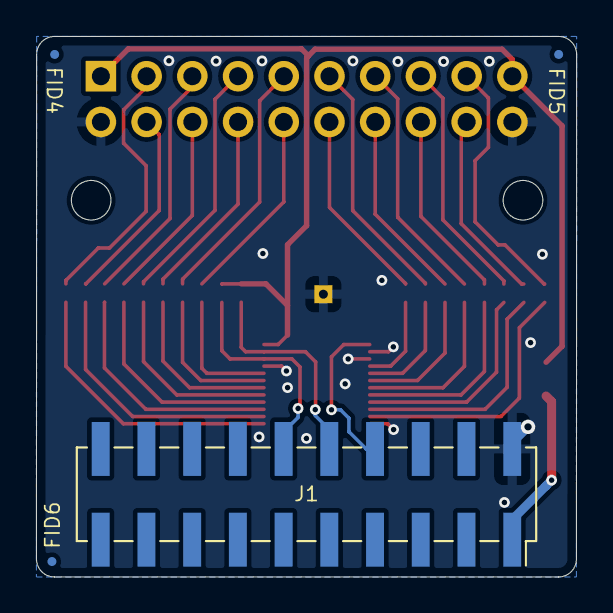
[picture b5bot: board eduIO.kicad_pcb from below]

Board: 2 copper layers, 30.0 x 30.0 mm, 36 parts (4 on the bottom side), 38 nets.

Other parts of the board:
kibuzzard-674D68C8: G***; kibuzzard-674D68C8
